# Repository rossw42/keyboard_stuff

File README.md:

# Keyboard Development Ecosystem

A collection of tools and resources for mechanical keyboard development - from hardware design through firmware implementation.

> **Disclaimer**: I'm not really a programmer, I dont even play one on GitHub. This entire repo is a perpetual work-in-progress that will probably never be "finished" - much like my quest for the perfect keyboard layout. Expect things to be broken, half-implemented, or completely abandoned as I chase the next shiny keyboard idea. 🤷‍♂️

## 🛠 What's Actually Here - that probably isn't all working.

### **ergogen/** - Ergogen-focused utilities for keyboard hardware design
- **ergogen-toolkit/** - Simple VS Code extension for running Ergogen and viewing DXF files - mostly working
- **ergogen_to_qmk_converter/** - Convert Ergogen YAML to QMK firmware configs (in development)
- **kle_to_ergogen/** - Transform KLE layouts to Ergogen point definitions  
- **mounting_styles/** - Reference implementations and examples for different mounting approaches
- **working_samples/** - Example Ergogen configurations and test cases

### **keyboards/** - Layout Configurations & Designs
Keyboard layouts and configurations that Im working on or have saved from somewhere else.
- VIA/QMK layout files for various keyboards (Lily58, Corne, DZ60, etc.)
- Custom macropad and encoder configurations
- JSON layout definitions for popular keyboards
- 3D files (STL, 3MF) for some designs

### **qmk_utilities/** - QMK Firmware Development Tools
QMK workflow utilities:
- **qmk_format_converter/** - Convert between KLE, VIA, keymap.c, and QMK Configurator formats (almost works!)
- **ascii_keymap_gen/** - Generate ASCII art representations of keyboard layouts in your QMK keymap files.

### **switch_research/** - Component Research & Documentation
Mechanical keyboard switch research:
- Comprehensive MX switch characteristics database
- Switch selection guides and comparison data

## 🤝 Contributing

Each project welcomes contributions! Common areas needing help:
- Bug fixes in format converters
- Additional keyboard layout examples  
- Switch database expansion
- Documentation improvements

Check individual README files for specific guidelines.

_"It's not a bug, it's a feature I haven't implemented yet."_

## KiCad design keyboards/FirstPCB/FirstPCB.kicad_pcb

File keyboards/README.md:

# keyboards

Welcome to the digital equivalent of that junk drawer in your kitchen. I dump alot of things here, mostly my via/vial keyboard configs. There are active projects here, there are dead ideas here and there are many keyboards that I have sold or given away.

> **Warning**: This folder is a mess. It has been *partially* cleaned up, but don't let that fool you. The chaos runs deep. 🕷️

---

## What's In Here

Each subdirectory is (roughly) a keyboard or project. Files *should* be in the folder for the keyboard they belong to. The word "should" is doing a lot of heavy lifting there.

| Folder | What It Probably Is |
|---|---|
| `Arisu/` | Arisu layout keymaps & PCB files |
| `Basketweave/` | Basketweave keymaps |
| `biaxial/` | BiAxial custom keyboard design (ergogen, KLE, DXF, STL) |
| `BM60_Poker/` | BM60 Poker layout files |
| `cocot46plus/` | aki27 cocot46plus trackball keyboard |
| `corne/`, `crkbd/`, `CorneLeft/`, `corneLP/` | Various Corne/CRKBD variants |
| `Discipline/` | Discipline65 build files, BOM, keymaps |
| `DZ60/` | DZ60 layout files |
| `egg58/`, `egg58 white/` | Eggsworks Egg58 keymaps (black & white versions) |
| `Lattice/` | Lattice60 build guide, VIA config, case files |
| `macropad/`, `macropadv2/` | Handwired macropad QMK firmware |
| `minivan/` | Minivan keymaps and configs |
| `mysterium/` | Mysterium TKL build files |
| `nuphy-air96-v2-via3/` | NuPhy Air96 V2 VIA config |
| `Romeo/` | Romeo build files, BOM CSVs, PCB, case models |
| `air60v2/`, `air75v2/` | NuPhy Air60/Air75 V2 layout files |
| `a_dux/` | A-Dux split keyboard |
| `3key/`, `4key/`, `3x4/`, `4x2/`, `2key/` | Small macropads and test boards |
| `sweep/`, `kyria/`, `lily58/`, `helix/`, `redox/` | Various split keyboards |
| `charybdis/`, `ploopy/` | Trackball/trackpad builds |
| `planckv7/` | Planck rev7 |
| ... and many more | It's a mess. See above. |

---

## The State of This Folder

Honestly? It's a mess. It has always been a mess. A partial cleanup was done on 2026-07-14 to move loose root-level files into their keyboard subdirectories, and orphaned/duplicate files into `archive/`. The underlying folder structure was not changed.

Organizational principles applied (loosely):
- Files named after a keyboard → moved into that keyboard's folder
- Duplicate files (newer copy in a subfolder) → moved to `archive/`
- Weird orphan DLLs, random JSONs, mystery ZIPs with no obvious home → also in `archive/`

## Disclaimer

- **Nothing is guaranteed to work** — but hey, that's half the fun!
---

*"It's not hoarding if it's keyboard files... right?"*

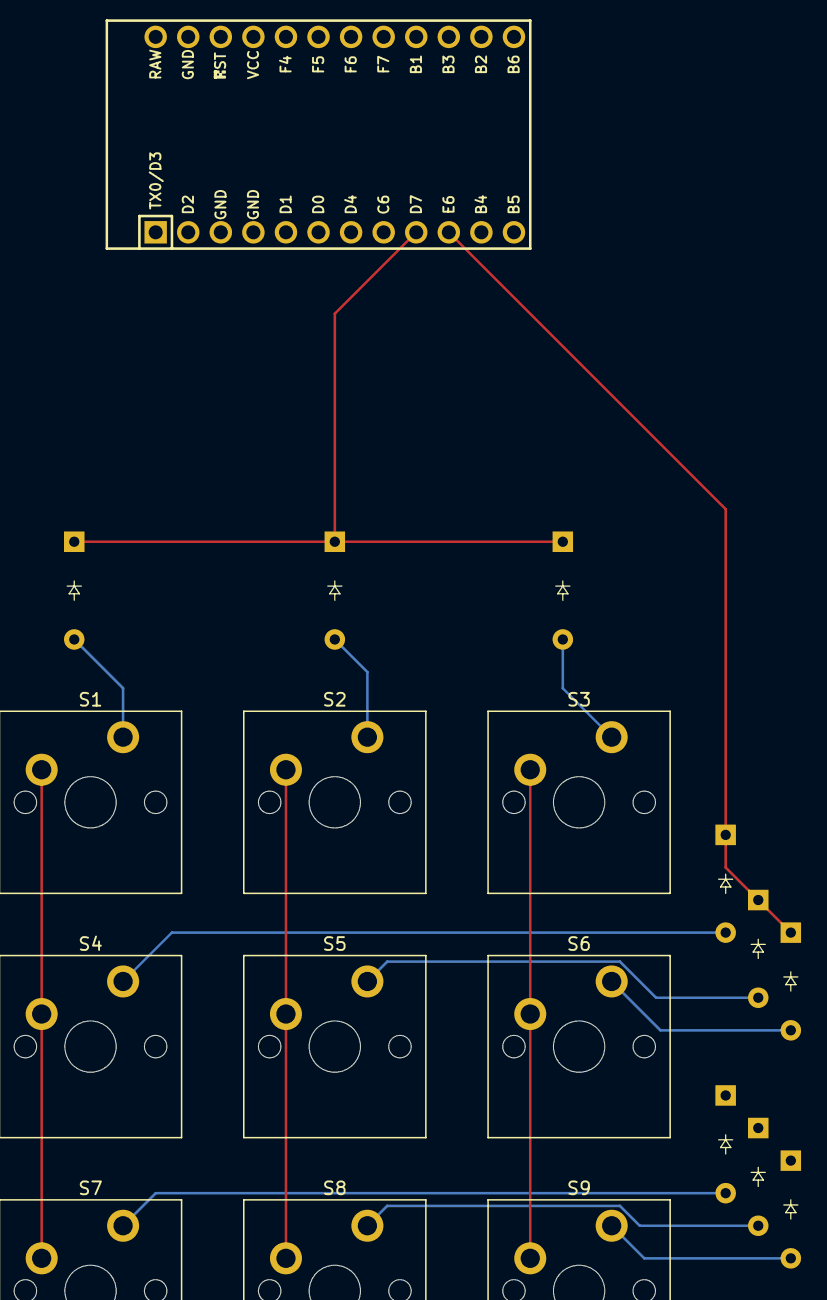
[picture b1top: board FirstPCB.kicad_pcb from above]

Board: 2 copper layers, 19 parts (0 on the bottom side), 15 nets.

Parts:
D1, D2, D3, D4, D5, D6, D7, D8, D9: Diode_DO-35
S1, S2, S3, S4, S5, S6, S7, S8, S9: MX_PCB_1.00u
U1: Arduino_Pro_Micro

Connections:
/Col 0: S1.1, S4.1, S7.1, U1.5 (2/PD1)
/Col 1: S2.1, S5.1, S8.1, U1.6 (3/PD0)
/Col 2: S3.1, S6.1, S9.1, U1.7 (4/PD4)
/Row 0: D1.1 (K), D2.1 (K), D3.1 (K), U1.9 (6/PD7)
/Row 1: D4.1 (K), D5.1 (K), D6.1 (K), U1.10 (7/PE6)
/Row 2: D7.1 (K), D8.1 (K), D9.1 (K), U1.11 (8/PB4)
unnamed: D1.2 (A), S1.2
unnamed: D2.2 (A), S2.2
unnamed: D3.2 (A), S3.2
unnamed: D4.2 (A), S4.2
unnamed: D5.2 (A), S5.2
unnamed: D6.2 (A), S6.2
unnamed: D7.2 (A), S7.2
unnamed: D8.2 (A), S8.2
unnamed: D9.2 (A), S9.2

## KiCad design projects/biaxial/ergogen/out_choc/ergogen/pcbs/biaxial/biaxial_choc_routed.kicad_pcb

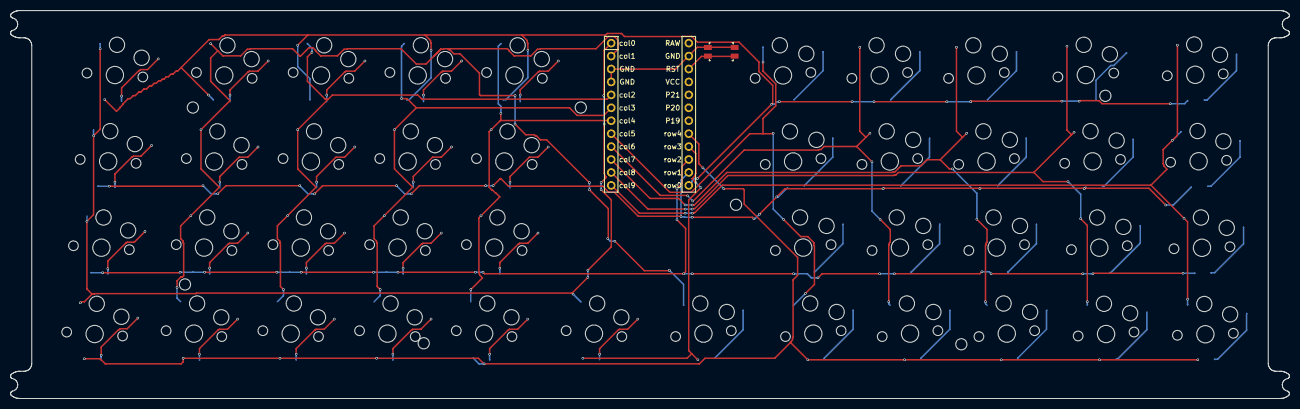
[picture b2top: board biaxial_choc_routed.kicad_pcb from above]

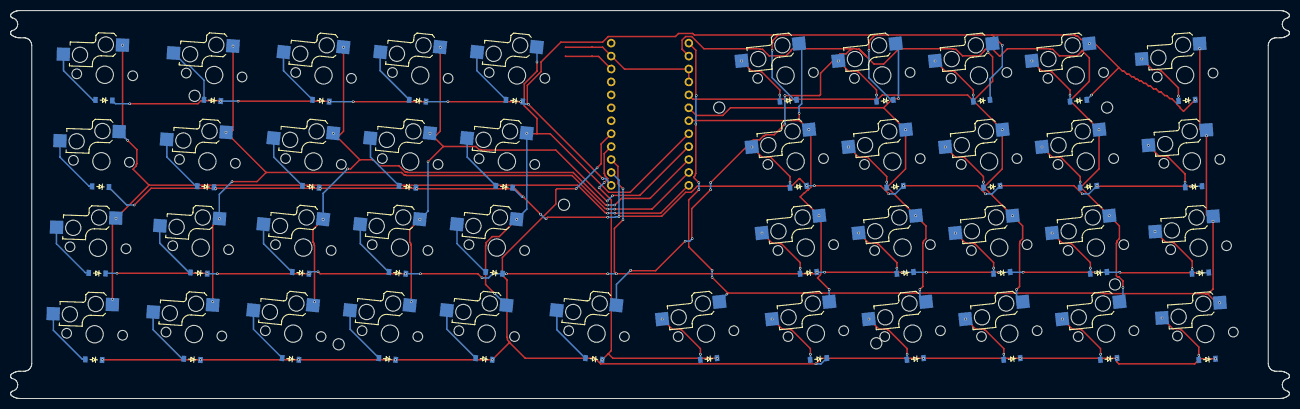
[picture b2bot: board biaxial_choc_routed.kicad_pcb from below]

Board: 2 copper layers, 251.2 x 76.2 mm, 93 parts (84 on the bottom side), 59 nets.

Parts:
D1, D2, D3, D4, D5, D6, D7, D8, D9, D10, D11, D12, D13, D14, D15, D16, D17, D18, D19, D20, D21, D22, D23, D24, D25, D26, D27, D28, D29, D30, D31, D32, D33, D34, D35, D36, D37, D38, D39, D40, D41, D42: diode_tht_sod123
MCU1: mcu_nice_nano
MH1, MH2, MH3, MH4, MH5, MH6, MH7: mounting_hole_npth
RST1: reset_switch_smd_side
S1, S2, S3, S4, S5, S6, S7, S8, S9, S10, S11, S12, S13, S14, S15, S16, S17, S18, S19, S20, S21, S22, S23, S24, S25, S26, S27, S28, S29, S30, S31, S32, S33, S34, S35, S36, S37, S38, S39, S40, S41, S42: switch_choc_v1_v2

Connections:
GND: MCU1.2, MCU1.21, MCU1.22, RST1.1, RST1.3
RST: MCU1.3, RST1.2, RST1.4
col0: MCU1.24, S1.1, S2.1, S3.1, S4.1, S41.1
col1: MCU1.23, S5.1, S6.1, S7.1, S8.1, S42.1
col2: MCU1.20, S9.1, S10.1, S11.1, S12.1
col3: MCU1.19, S13.1, S14.1, S15.1, S16.1
col4: MCU1.18, S17.1, S18.1, S19.1, S20.1
col5: MCU1.17, S21.1, S22.1, S23.1, S24.1
col6: MCU1.16, S25.1, S26.1, S27.1, S28.1
col7: MCU1.15, S29.1, S30.1, S31.1, S32.1
col8: MCU1.14, S33.1, S34.1, S35.1, S36.1
col9: MCU1.13, S37.1, S38.1, S39.1, S40.1
key_r0c0: D1.2, S1.2
key_r0c1: D5.2, S5.2
key_r0c2: D9.2, S9.2
key_r0c3: D13.2, S13.2
key_r0c4: D17.2, S17.2
key_r0c5: D21.2, S21.2
key_r0c6: D25.2, S25.2
key_r0c7: D29.2, S29.2
key_r0c8: D33.2, S33.2
key_r0c9: D37.2, S37.2
key_r1c0: D2.2, S2.2
key_r1c1: D6.2, S6.2
key_r1c2: D10.2, S10.2
key_r1c3: D14.2, S14.2
key_r1c4: D18.2, S18.2
key_r1c5: D22.2, S22.2
key_r1c6: D26.2, S26.2
key_r1c7: D30.2, S30.2
key_r1c8: D34.2, S34.2
key_r1c9: D38.2, S38.2
key_r2c0: D3.2, S3.2
key_r2c1: D7.2, S7.2
key_r2c2: D11.2, S11.2
key_r2c3: D15.2, S15.2
key_r2c4: D19.2, S19.2
key_r2c5: D23.2, S23.2
key_r2c6: D27.2, S27.2
key_r2c7: D31.2, S31.2
key_r2c8: D35.2, S35.2
key_r2c9: D39.2, S39.2
key_r3c0: D41.2, S41.2
key_r3c1: D42.2, S42.2
key_r4c0: D4.2, S4.2
key_r4c1: D8.2, S8.2
key_r4c2: D12.2, S12.2
key_r4c3: D16.2, S16.2
key_r4c4: D20.2, S20.2
key_r4c5: D24.2, S24.2
key_r4c6: D28.2, S28.2
key_r4c7: D32.2, S32.2
key_r4c8: D36.2, S36.2
key_r4c9: D40.2, S40.2
row0: D1.1, D5.1, D9.1, D13.1, D17.1, D21.1, D25.1, D29.1, D33.1, D37.1, MCU1.12
row1: D2.1, D6.1, D10.1, D14.1, D18.1, D22.1, D26.1, D30.1, D34.1, D38.1, MCU1.11
row2: D3.1, D7.1, D11.1, D15.1, D19.1, D23.1, D27.1, D31.1, D35.1, D39.1, MCU1.10
row3: D41.1, D42.1, MCU1.9
row4: D4.1, D8.1, D12.1, D16.1, D20.1, D24.1, D28.1, D32.1, D36.1, D40.1, MCU1.8

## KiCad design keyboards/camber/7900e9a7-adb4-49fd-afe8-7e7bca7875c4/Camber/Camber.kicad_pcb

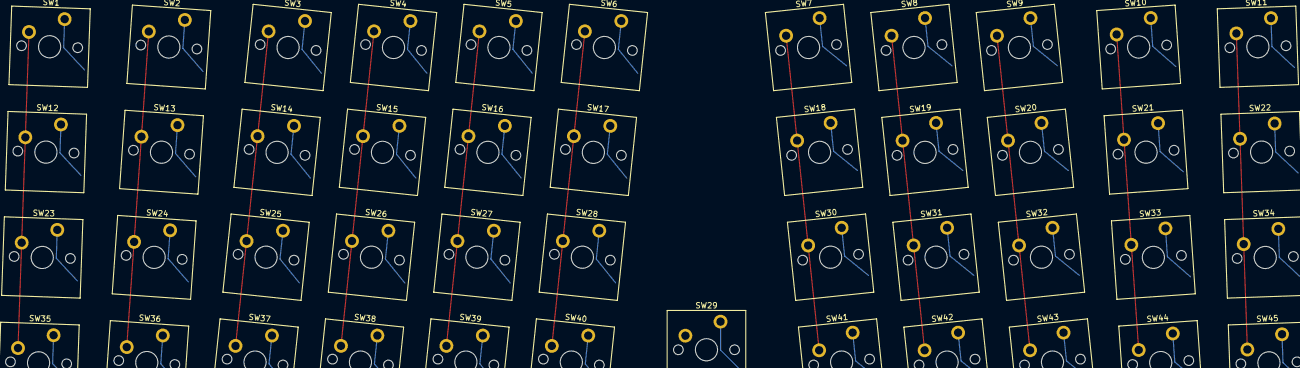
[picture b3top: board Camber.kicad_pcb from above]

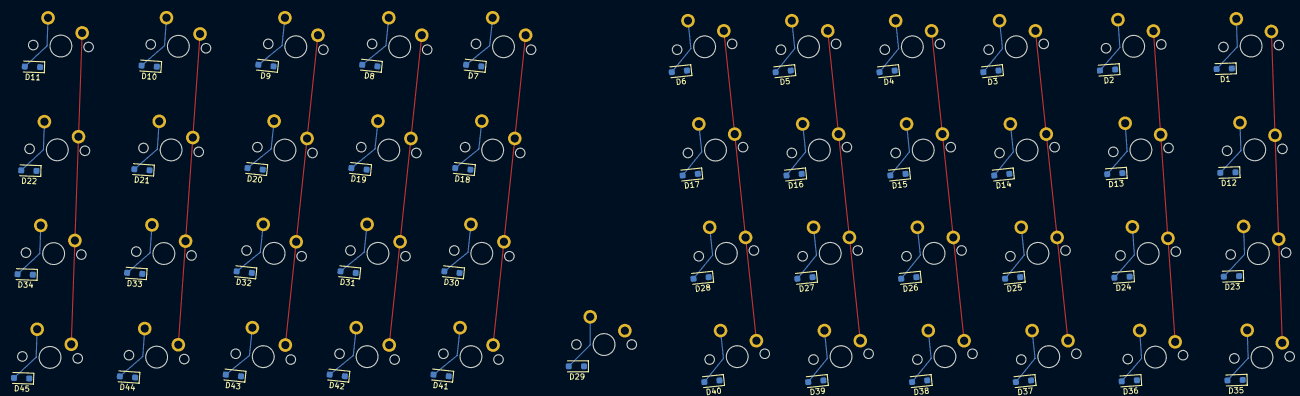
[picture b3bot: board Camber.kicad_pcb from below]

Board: 2 copper layers, 90 parts (45 on the bottom side), 60 nets.

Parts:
D1, D2, D3, D4, D5, D6, D7, D8, D9, D10, D11, D12, D13, D14, D15, D16, D17, D18, D19, D20, D21, D22, D23, D24, D25, D26, D27, D28, D29, D30, D31, D32, D33, D34, D35, D36, D37, D38, D39, D40, D41, D42, D43, D44, D45: D; D_SOD-123F
SW1, SW2, SW3, SW4, SW5, SW6, SW7, SW8, SW9, SW10, SW11, SW12, SW13, SW14, SW15, SW16, SW17, SW18, SW19, SW20, SW21, SW22, SW23, SW24, SW25, SW26, SW27, SW28, SW29, SW30, SW31, SW32, SW33, SW34, SW35, SW36, SW37, SW38, SW39, SW40, SW41, SW42, SW43, SW44, SW45: SW_Push; SW_Cherry_MX_PCB_1.00u

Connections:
COL0: SW1.1, SW12.1, SW23.1, SW35.1
COL1: SW2.1, SW13.1, SW24.1, SW36.1
COL2: SW3.1, SW14.1, SW25.1, SW37.1
COL3: SW4.1, SW15.1, SW26.1, SW38.1
COL4: SW5.1, SW16.1, SW27.1, SW39.1
COL5: SW6.1, SW17.1, SW28.1, SW40.1
COL7: SW7.1, SW18.1, SW30.1, SW41.1
COL8: SW8.1, SW19.1, SW31.1, SW42.1
COL9: SW9.1, SW20.1, SW32.1, SW43.1
COL10: SW10.1, SW21.1, SW33.1, SW44.1
COL11: SW11.1, SW22.1, SW34.1, SW45.1
unnamed: D1.2 (A), SW1.2
unnamed: D2.2 (A), SW2.2
unnamed: D3.2 (A), SW3.2
unnamed: D4.2 (A), SW4.2
unnamed: D5.2 (A), SW5.2
unnamed: D6.2 (A), SW6.2
unnamed: D7.2 (A), SW7.2
unnamed: D8.2 (A), SW8.2
unnamed: D9.2 (A), SW9.2
unnamed: D10.2 (A), SW10.2
unnamed: D11.2 (A), SW11.2
unnamed: D12.2 (A), SW12.2
unnamed: D13.2 (A), SW13.2
unnamed: D14.2 (A), SW14.2
unnamed: D15.2 (A), SW15.2
unnamed: D16.2 (A), SW16.2
unnamed: D17.2 (A), SW17.2
unnamed: D18.2 (A), SW18.2
unnamed: D19.2 (A), SW19.2
unnamed: D20.2 (A), SW20.2
unnamed: D21.2 (A), SW21.2
unnamed: D22.2 (A), SW22.2
unnamed: D23.2 (A), SW23.2
unnamed: D24.2 (A), SW24.2
unnamed: D25.2 (A), SW25.2
unnamed: D26.2 (A), SW26.2
unnamed: D27.2 (A), SW27.2
unnamed: D28.2 (A), SW28.2
unnamed: D29.2 (A), SW29.2
unnamed: D30.2 (A), SW30.2
unnamed: D31.2 (A), SW31.2
unnamed: D32.2 (A), SW32.2
unnamed: D33.2 (A), SW33.2
unnamed: D34.2 (A), SW34.2
unnamed: D35.2 (A), SW35.2
unnamed: D36.2 (A), SW36.2
unnamed: D37.2 (A), SW37.2
unnamed: D38.2 (A), SW38.2
unnamed: D39.2 (A), SW39.2
unnamed: D40.2 (A), SW40.2
unnamed: D41.2 (A), SW41.2
unnamed: D42.2 (A), SW42.2
unnamed: D43.2 (A), SW43.2
unnamed: D44.2 (A), SW44.2
unnamed: D45.2 (A), SW45.2
ROW0: D1.1 (K), D2.1 (K), D3.1 (K), D4.1 (K), D5.1 (K), D6.1 (K), D7.1 (K), D8.1 (K), D9.1 (K), D10.1 (K), D11.1 (K)
ROW1: D12.1 (K), D13.1 (K), D14.1 (K), D15.1 (K), D16.1 (K), D17.1 (K), D18.1 (K), D19.1 (K), D20.1 (K), D21.1 (K), D22.1 (K)
ROW2: D23.1 (K), D24.1 (K), D25.1 (K), D26.1 (K), D27.1 (K), D28.1 (K), D29.1 (K), D30.1 (K), D31.1 (K), D32.1 (K), D33.1 (K), D34.1 (K)
ROW3: D35.1 (K), D36.1 (K), D37.1 (K), D38.1 (K), D39.1 (K), D40.1 (K), D41.1 (K), D42.1 (K), D43.1 (K), D44.1 (K), D45.1 (K)

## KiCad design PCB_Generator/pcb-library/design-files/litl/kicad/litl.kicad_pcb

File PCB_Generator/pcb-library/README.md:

# Through-Hole Keyboard PCB Library

A curated collection of 11 open-source through-hole mechanical keyboard PCB designs. All designs are manufacturing-ready with complete documentation, BOMs, and firmware support.

## Overview

This library contains proven PCB designs for various keyboard form factors, all using through-hole components for easy assembly and aesthetic appeal.

## Available Designs

### 60% Keyboards
- **Discipline** - ATmega32A, USB-C, QMK/VIA
- **Mysterium** - ATmega328P, USB-C, QMK/VIA
- **Lumberjack** - ATmega328P, ortholinear

### 65% Keyboards
- **KBD67 Lite** - Through-hole variant

### 40% Keyboards
- **Plaid** - ATmega328P, minimal design
- **Litl** - Pro Micro, compact

### Numpads
- **Discipline Numpad** - Standalone numpad
- **Plaid Numpad** - Minimal numpad

### Macropads
- **9-Key Macropad** - 3x3 grid
- **12-Key Macropad** - 3x4 grid
- **16-Key Macropad** - 4x4 grid

## Directory Structure

```
pcb-library/
├── design-files/          # KiCad source files
│   ├── discipline/
│   ├── mysterium/
│   └── ...
│
├── gerbers/               # Manufacturing files
│   ├── discipline/
│   └── ...
│
├── boms/                  # Bills of materials
│   ├── master-bom.csv    # Consolidated BOM
│   └── individual/
│
├── firmware/              # QMK firmware configs
│   ├── discipline/
│   └── ...
│
├── docs/                  # Documentation
│   ├── build-guides/
│   ├── compatible_pcbs.md
│   └── gh60_pcb_specifications.md
│
├── 3d-models/             # 3D models (STEP, STL)
├── templates/             # Circuit templates
└── scripts/               # Utility scripts
```

## Quick Start

### Browse Designs
```bash
cat PROJECT_CATALOG.md
```

### View a Design
```bash
# Open in KiCad
kicad design-files/discipline/discipline.kicad_pro
```

### Order PCBs
```bash
# Gerbers are ready to upload to:
# - JLCPCB
# - PCBWay
# - OSH Park
# - etc.

# Find gerbers in: gerbers/[project-name]/
```

## Features

### All Designs Include
- ✅ Complete KiCad schematics
- ✅ Manufacturing-ready Gerbers
- ✅ Detailed BOMs with part numbers
- ✅ QMK firmware support
- ✅ Build guides
- ✅ 3D models

### Common Specifications
- **Components:** Through-hole only
- **MCUs:** ATmega328P, ATmega32A, Pro Micro
- **USB:** USB-C, Mini, Micro (through-hole)
- **Firmware:** QMK, VIA, VIAL support
- **Diodes:** 1N4148 through-hole
- **Switches:** Cherry MX compatible

## Documentation

### Library Documentation
- **Project Catalog:** [PROJECT_CATALOG.md](PROJECT_CATALOG.md)
- **File Index:** [FILE_INDEX.md](FILE_INDEX.md)
- **Project Status:** [PROJECT_STATUS.md](PROJECT_STATUS.md)
- **Component Reference:** [components.md](components.md)
- **References:** [references.md](references.md)
- **Contributing:** [CONTRIBUTING.md](CONTRIBUTING.md)

### PCB Design Guides
- **📘 PCB Design Guide:** [docs/PCB_DESIGN_GUIDE.md](docs/PCB_DESIGN_GUIDE.md) - Comprehensive wired keyboard PCB design
- **📻 Wireless PCB Guide:** [docs/WIRELESS_PCB_DESIGN.md](docs/WIRELESS_PCB_DESIGN.md) - nRF52840/ZMK wireless design
- **✅ Design Checklist:** [docs/PCB_DESIGN_CHECKLIST.md](docs/PCB_DESIGN_CHECKLIST.md) - Step-by-step checklist
- **🔌 Schematic Patterns:** [docs/SCHEMATIC_PATTERNS.md](docs/SCHEMATIC_PATTERNS.md) - Actual circuit examples from library projects

## Using These Designs

### For Building
1. Choose a design from PROJECT_CATALOG.md
2. Download Gerbers from gerbers/[project]/
3. Order PCBs from your preferred manufacturer
4. Follow build guide in docs/build-guides/
5. Flash firmware from firmware/[project]/

### For Modification
1. Open design-files/[project]/ in KiCad
2. Modify as needed
3. Export new Gerbers
4. Update BOM if components changed

### For Reference
- Use as templates for new designs
- Extract circuit blocks (see templates/)
- Study proven implementations

## Component Sourcing

See [boms/master-bom.csv](boms/master-bom.csv) for:
- Consolidated component list
- Vendor part numbers (Mouser, Digikey)
- Pricing information
- Alternative parts

## Firmware

All designs support QMK firmware. Pre-configured firmware available in firmware/ directory.

### Flash Firmware
```bash
# Using QMK CLI
qmk flash -kb [keyboard] -km default

# Or use QMK Toolbox (GUI)
```

## Manufacturing Notes

- **PCB Thickness:** 1.6mm standard
- **Copper Weight:** 1oz (35μm)
- **Surface Finish:** HASL or ENIG
- **Solder Mask:** Any color
- **Silkscreen:** White recommended

## Contributing

See [CONTRIBUTING.md](CONTRIBUTING.md) for:
- Adding new designs
- Improving documentation
- Reporting issues
- Submitting corrections

## License

Each design has its own license. See individual project directories for details. Most are open-source (MIT, GPL, CC-BY-SA).

## Credits

These designs are from the open-source keyboard community. Original designers are credited in each project directory.

---

**Need Help?**
- Build issues? Check docs/build-guides/
- Component questions? See components.md
- PCB compatibility? See docs/compatible_pcbs.md

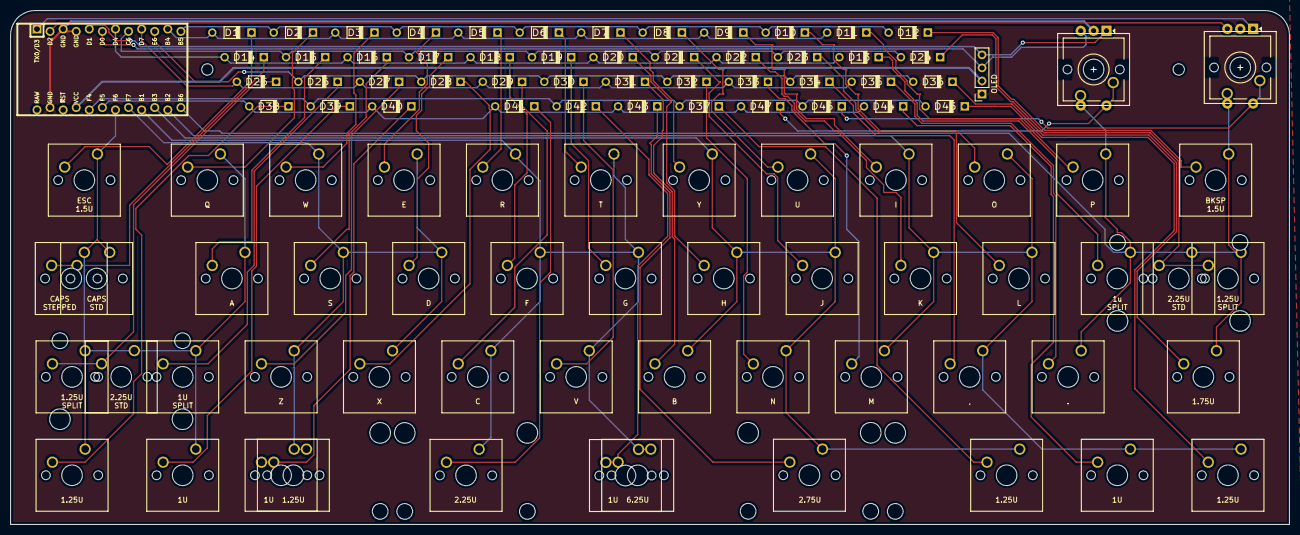
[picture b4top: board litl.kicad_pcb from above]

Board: 2 copper layers, 248.3 x 99.8 mm, 103 parts (1 on the bottom side), 67 nets.

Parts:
D1, D2, D3, D4, D5, D6, D7, D8, D9, D10, D11, D12, D13, D14, D15, D16, D17, D18, D19, D20, D21, D22, D23, D24, D25, D26, D27, D28, D29, D30, D31, D32, D33, D34, D35, D36, D37, D38, D39, D40, D41, D42, D43, D44, D45, D46, D47: D_Small; Diode
J1: Conn_01x04; PinSocket_1x04_P2.54mm_Vertical
SW1, SW12: KEYSW; SW_Cherry_MX_1.50u_PCB
SW2, SW3, SW4, SW5, SW6, SW7, SW8, SW9, SW10, SW11, SW15, SW16, SW17, SW18, SW19, SW20, SW21, SW22, SW23, SW24, SW25, SW29, SW30, SW31, SW32, SW33, SW34, SW35, SW36, SW37, SW38, SW40, SW41, SW44, SW49, SW52, SW54: KEYSW; SW_Cherry_MX_1.00u_PCB
SW13, SW28, SW42, SW43, SW45, SW50: KEYSW; SW_Cherry_MX_1.25u_PCB
SW14, SW39: KEYSW; SW_Cherry_MX_1.75u_PCB
SW26, SW27, SW46: KEYSW; SW_Cherry_MX_2.25u_PCB
SW47: KEYSW; SW_Cherry_MX_6.25u_PCB
SW48: KEYSW; SW_Cherry_MX_2.75u_PCB
SW51, SW53: RotaryEncoder_Switch; RotaryEncoder_EC11
U1: ProMicro; ArduinoProMicro-ZigZag

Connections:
GND: J1.1, SW51.C, SW53.C, U1.3 (GND), U1.4 (GND), U1.23 (GND)
unnamed: D1.2 (A), SW1.2
unnamed: D2.2 (A), SW2.2
unnamed: D3.2 (A), SW3.2
unnamed: D4.2 (A), SW4.2
unnamed: D5.2 (A), SW5.2
unnamed: D6.2 (A), SW6.2
unnamed: D7.2 (A), SW7.2
unnamed: D8.2 (A), SW8.2
unnamed: D9.2 (A), SW9.2
unnamed: D10.2 (A), SW10.2
unnamed: D11.2 (A), SW11.2
unnamed: D12.2 (A), SW12.2
unnamed: D13.2 (A), SW25.2
unnamed: D14.2 (A), SW14.2, SW15.2
unnamed: D15.2 (A), SW16.2
unnamed: D16.2 (A), SW17.2
unnamed: D17.2 (A), SW18.2
unnamed: D18.2 (A), SW19.2
unnamed: D19.2 (A), SW20.2
unnamed: D20.2 (A), SW21.2
unnamed: D21.2 (A), SW22.2
unnamed: D22.2 (A), SW23.2
unnamed: D23.2 (A), SW24.2
unnamed: D24.2 (A), SW13.2, SW26.2
unnamed: D25.2 (A), SW27.2, SW28.2
unnamed: D26.2 (A), SW29.2
unnamed: D27.2 (A), SW30.2
unnamed: D28.2 (A), SW31.2
unnamed: D29.2 (A), SW32.2
unnamed: D30.2 (A), SW33.2
unnamed: D31.2 (A), SW34.2
unnamed: D32.2 (A), SW35.2
unnamed: D33.2 (A), SW36.2
unnamed: D34.2 (A), SW37.2
unnamed: D35.2 (A), SW38.2
unnamed: D36.2 (A), SW39.2
unnamed: D37.2 (A), SW42.2
unnamed: D38.2 (A), SW43.2
unnamed: D39.2 (A), SW44.2
unnamed: D40.2 (A), SW40.2, SW45.2
unnamed: D41.2 (A), SW46.2
unnamed: D42.2 (A), SW41.2, SW47.2
unnamed: D43.2 (A), SW48.2
unnamed: D44.2 (A), SW49.2
unnamed: D45.2 (A), SW50.2
RotA: D46.2 (A), SW51.S2, SW54.2
RotB: SW11.1, SW12.1, SW13.1, SW25.1, SW26.1, SW38.1, SW39.1, SW51.S1, SW52.1, SW53.S1, SW54.1, U1.13 (10/PB6)
RotC: D47.2 (A), SW52.2, SW53.S2
SCL: J1.3, SW53.B, U1.6 (3/PD0)
SDA: J1.4, SW53.A, U1.5 (2/PD1)
VCC: J1.2, U1.21 (VCC)
col0: SW1.1, SW2.1, SW14.1, SW15.1, SW16.1, SW27.1, SW28.1, SW29.1, SW43.1, SW44.1, U1.18 (A1/PF6)
col1: SW3.1, SW4.1, SW17.1, SW18.1, SW30.1, SW31.1, SW40.1, SW45.1, U1.17 (A0/PF7)
col2: SW5.1, SW6.1, SW19.1, SW20.1, SW32.1, SW33.1, SW41.1, SW46.1, SW47.1, U1.16 (15/PB1)
col3: SW7.1, SW8.1, SW21.1, SW22.1, SW34.1, SW35.1, SW42.1, SW48.1, U1.15 (14/PB3)
col4: SW9.1, SW10.1, SW23.1, SW24.1, SW36.1, SW37.1, SW49.1, SW50.1, U1.14 (16/PB2)
encA: SW51.A, U1.1 (TX0/PD3)
encB: SW51.B, U1.2 (RX1/PD2)
rowA: D1.1 (K), D3.1 (K), D5.1 (K), D7.1 (K), D9.1 (K), D11.1 (K), U1.11 (8/PB4)
rowB: D2.1 (K), D4.1 (K), D6.1 (K), D8.1 (K), D10.1 (K), D12.1 (K), U1.12 (9/PB5)
rowC: D13.1 (K), D14.1 (K), D16.1 (K), D18.1 (K), D20.1 (K), D22.1 (K), U1.7 (4/PD4)
rowD: D15.1 (K), D17.1 (K), D19.1 (K), D21.1 (K), D23.1 (K), D24.1 (K), U1.8 (5/PC6)
rowE: D25.1 (K), D27.1 (K), D29.1 (K), D31.1 (K), D33.1 (K), D35.1 (K), U1.9 (6/PD7)
rowF: D26.1 (K), D28.1 (K), D30.1 (K), D32.1 (K), D34.1 (K), D36.1 (K), U1.10 (7/PE6)
rowG: D38.1 (K), D40.1 (K), D41.1 (K), D43.1 (K), D44.1 (K), D47.1 (K), U1.19 (A2/PF5)
rowH: D37.1 (K), D39.1 (K), D42.1 (K), D45.1 (K), D46.1 (K), U1.20 (A3/PF4)

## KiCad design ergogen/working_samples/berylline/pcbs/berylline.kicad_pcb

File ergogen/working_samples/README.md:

# Ergogen Working Samples

A curated collection of community Ergogen keyboard configs used as reference patterns for the toolkit. These are proven, real-world configurations — when writing a new config, start from the closest sample here.

## Provenance

Collected **October 22, 2025** via a GitHub API survey that found **123 Ergogen repositories** (full list: [`../docs/research/ergogen_repos_list.md`](../docs/research/ergogen_repos_list.md)). Notable star counts at the time: samoklava 379⭐, cephalopoda 232⭐, Kaly 209⭐, corax 131⭐, absolem 127⭐, mantis 117⭐, trochilidae 112⭐.

## Categories

### `minimal/` — small, easy-to-read configs
| Folder | Keyboard | Notes |
|---|---|---|
| `cephalopoda_idiosepius` | Cephalopoda Idiosepius | minimal split family member |
| `tern` | Tern | compact ergo |
| `tiny20` | Tiny20 | 20-key mini |
| `trochilidae_berylline` | Trochilidae Berylline | hummingbird recreation |
| `trochilidae_rufous` | Trochilidae Rufous | hummingbird recreation |

### `split/` — split keyboards
| Folder | Keyboard |
|---|---|
| `archimedes_tux` | Archimedes Tux |
| `cephalopoda_architeuthis` | Cephalopoda Architeuthis |
| `cephalopoda_dosidicus` | Cephalopoda Dosidicus |
| `jonkey` | Jonkey |
| `kaly` | Kaly (209⭐) |
| `nwsplit60` | NWSplit60 |
| `samoklava` | Samoklava (379⭐) |
| `uwb_electronics_club` | UWB Electronics Club board |

### `unibody/` — one-piece ergo boards
| Folder | Keyboard |
|---|---|
| `absolem` | Absolem (the original Ergogen keyboard) — simplified version |
| `mantis` | Mantis (hex-key layout) |
| `travis_ergogen_2024` | Travis's 2024 Ergogen build |

### `advanced/` — feature-rich configs
| Folder | Keyboard |
|---|---|
| `corax56` | Corax56 — PCB-generation variant |

### `tutorial/`
| Folder | Content |
|---|---|
| `chonkv` | ChonkV — used in tutorial walkthroughs |

### `uncategorized/` — pending sorting
Loose configs formerly at the root of this folder. **Some differ from same-named categorized versions — they are NOT confirmed duplicates** (e.g., `absolem.yaml` here is the full 972-line original; `unibody/absolem/config.yaml` is a 173-line simplified version; `corax56.yaml` here is an outlines/case variant vs. the PCB variant in `advanced/`). Sort or diff before deleting anything.

Includes: `absolem.yaml`, `samoklava.yaml`, `config.yaml` (identical to samoklava.yaml), `corax56.yaml`, `corney-island.yaml`, `LambBT.yaml`, `Lintilla.yaml`, `owl.yaml`, `porcupine_6x3.yaml`, `splave-ferris.yml`, `tempest.yaml`, `travis-ergogen-numpad.yml`, `tutorial.yml`, `Wubbo.yaml`, `ai_generated_numpad.yaml` (formerly misnamed `mantis.yaml` — an AI-generated numpad, not the Mantis keyboard).

## Housekeeping notes

- Generated build artifacts (tutorial DXF/JSCAD outputs) and confirmed duplicates were moved to [`../archive/working_samples/`](../archive/working_samples/) during the 2026-07 consolidation.
- This README absorbs the useful content of the former root `COLLECTION_SUMMARY.md`.

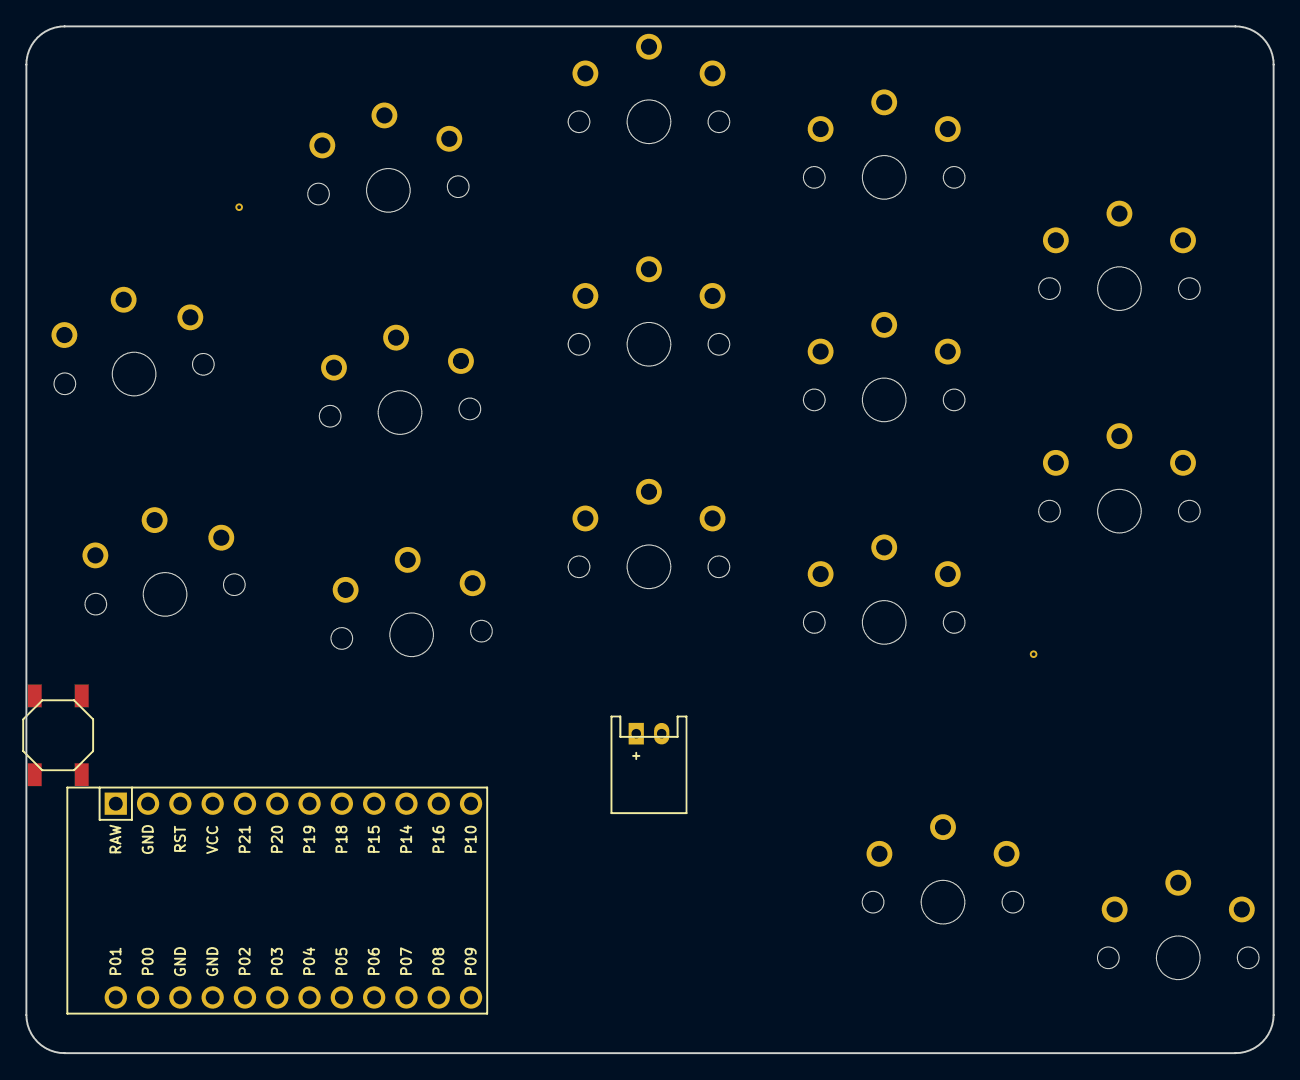
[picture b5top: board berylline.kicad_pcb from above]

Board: 2 copper layers, 98.1 x 80.8 mm, 18 parts (0 on the bottom side), 18 nets, no tracks yet.

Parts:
B1: SW_TACT_ALPS_SKQGABE010
JST1: JST_PH_S2B-PH-K_02x2.00mm_Angled
MCU1: ProMicro
S1, S2, S3, S4, S5, S6, S7, S8, S9, S10, S11, S12, S13, S14, S15: PG1350

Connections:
GND: B1.2, JST1.2, MCU1.2, MCU1.15, MCU1.16, S1.1, S2.1, S3.1, S4.1, S5.1, S6.1, S7.1, S8.1, S9.1, S10.1, S11.1, S12.1, S13.1, S14.1, S15.1
RAW: JST1.1, MCU1.1
RST: B1.1, MCU1.3
matrix_index_bottom: MCU1.20, S9.2
matrix_index_home: MCU1.19, S10.2
matrix_index_top: MCU1.18, S11.2
matrix_inner_home: MCU1.22, S12.2
matrix_inner_top: MCU1.21, S13.2
matrix_middle_bottom: MCU1.12, S6.2
matrix_middle_home: MCU1.11, S7.2
matrix_middle_top: MCU1.10, S8.2
matrix_pinky_home: MCU1.6, S1.2
matrix_pinky_top: MCU1.5, S2.2
matrix_ring_bottom: MCU1.9, S3.2
matrix_ring_home: MCU1.8, S4.2
matrix_ring_top: MCU1.7, S5.2
thumb_reachy: MCU1.23, S15.2
thumb_tucky: MCU1.24, S14.2

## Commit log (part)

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2025-08-09 Initial commit: Consolidate keyboard-related repositories
2025-08-09 Add all keyboard project files as regular directories
2025-08-09 Add humor and realistic expectations to README
2025-08-09 Apply Kiro IDE autofix/formatting to README
2025-08-09 Reorganize directory structure and clean up node_modules
2025-08-09 Move DXF viewer utilities from qmk_utilities to ergogen directory
2025-08-09 Update README to reflect new directory structure with DXF tools and switch research
2025-08-09 Apply Kiro IDE formatting to README
2025-08-10 working on mounting styles
2025-08-10 updade the mounting style readme
2025-08-11 building the ergogen-toolkit
2025-08-11 more changes
2025-08-11 worked on mounting styles ergogen
2025-08-13 More work on ergogen toolkit
2025-08-13 Working ergogen-toolkit
2025-08-14 Cleaning up local files
2025-08-14 adding more switches
2025-08-14 Updating Switch Research - enjoy
2025-08-14 Added readme
2025-08-14 Fixed links
2025-08-14 Fixing links v2
2025-08-14 Maybe fixed the links
2025-08-14 More updates
2025-08-14 Updating readmes
2025-08-14 Woking on QMK Converter
2025-08-16 A layout for VIA - to Play Cities Skylines 2
2025-08-16 More updates to the macropad
2025-08-18 Clean up forest and created a new ergogen script
2025-08-20 testing out a arrow macropad with encoder and thumbkey
2025-08-25 KDB67 Via file
2025-08-28 Some bad Lily58 OpenScad
2025-09-03 QMK matrix generator
2025-09-19 cleaning up
2025-09-19 moved some of the mouse functions around
2025-09-25 keymap drawer updates
2025-09-26 making up some keymap drawer configs
2025-09-26 Clean up many things
2025-10-02 adding lily58 vial
2025-10-15 Lily58 - new autogenerated keymap for vial
2025-10-17 adding z,x,c,v macros to layer 1 on air75v2
2025-10-20 Created BOM for Lattice from (Original PDF)
2025-10-21 Air75 mappings
2025-10-21 Trying to make a PCB generator - and failing
2025-10-22 Adding more configs
2025-10-23 Able to generate ergogen
2025-11-03 some planck mappings
2025-11-03 Lattice BOM updates
2025-11-11 CorneLeft City Skylines 2 keymap
2025-11-13 Making CorneLeft VIA CS2 keymap
2025-11-14 HyperGarlic Case Generation
2025-11-14 More Case generation
2025-11-18 Work on case gen
2025-11-19 CorneLeft Updates
2025-11-19 Found it
2025-11-19 Adding new planck vial keymap chages
2025-11-21 Working on the DGigas
2025-11-25 DG Case Gen
2025-11-25 tried to get OM ergogen to gen a case
2025-11-26 catchup
2025-11-26 dg keymap updates and keymap drawer script - move later
2026-01-09 Moving files around - adding switch chooser
2026-01-09 Add initial content to README.md
2026-04-14 bunch of changes
2026-04-14 mass changes
2026-04-14 camber files
2026-04-24 trying for v2
2026-05-18 big bulk push
2026-05-23 Pushing Cocot46plus files
